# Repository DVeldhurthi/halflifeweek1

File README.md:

# Half-Life Week 1: Design a PCB

Earlier two-layer BeginnerFC layout. The current CAD files in this repository are the four-layer Week1 design.

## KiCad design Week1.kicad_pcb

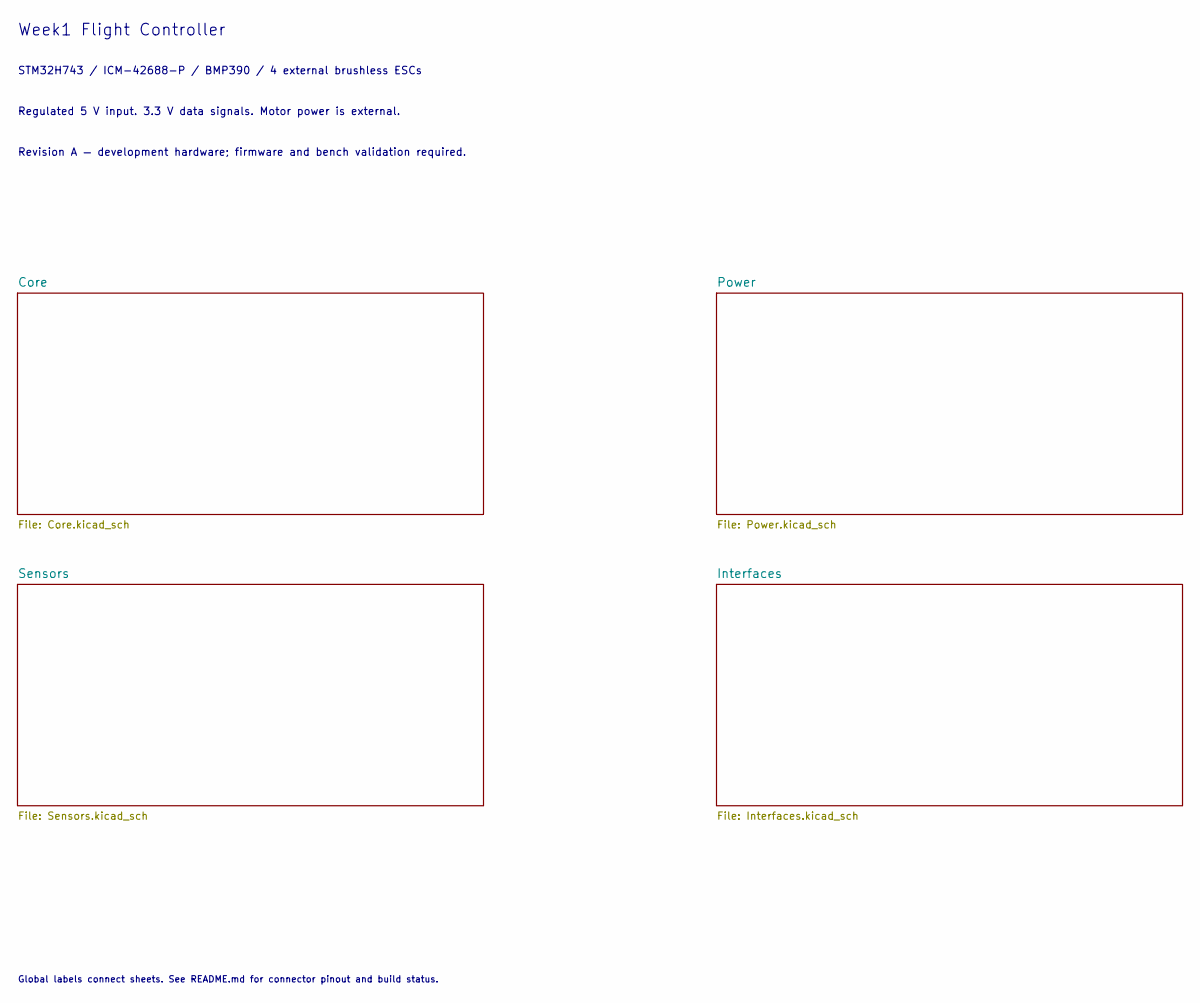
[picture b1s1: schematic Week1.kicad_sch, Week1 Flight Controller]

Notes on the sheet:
Week1 Flight Controller
STM32H743 / ICM-42688-P / BMP390 / 4 external brushless ESCs
Regulated 5 V input. 3.3 V data signals. Motor power is external.
Revision A — development hardware; firmware and bench validation required.
Global labels connect sheets. See README.md for connector pinout and build status.

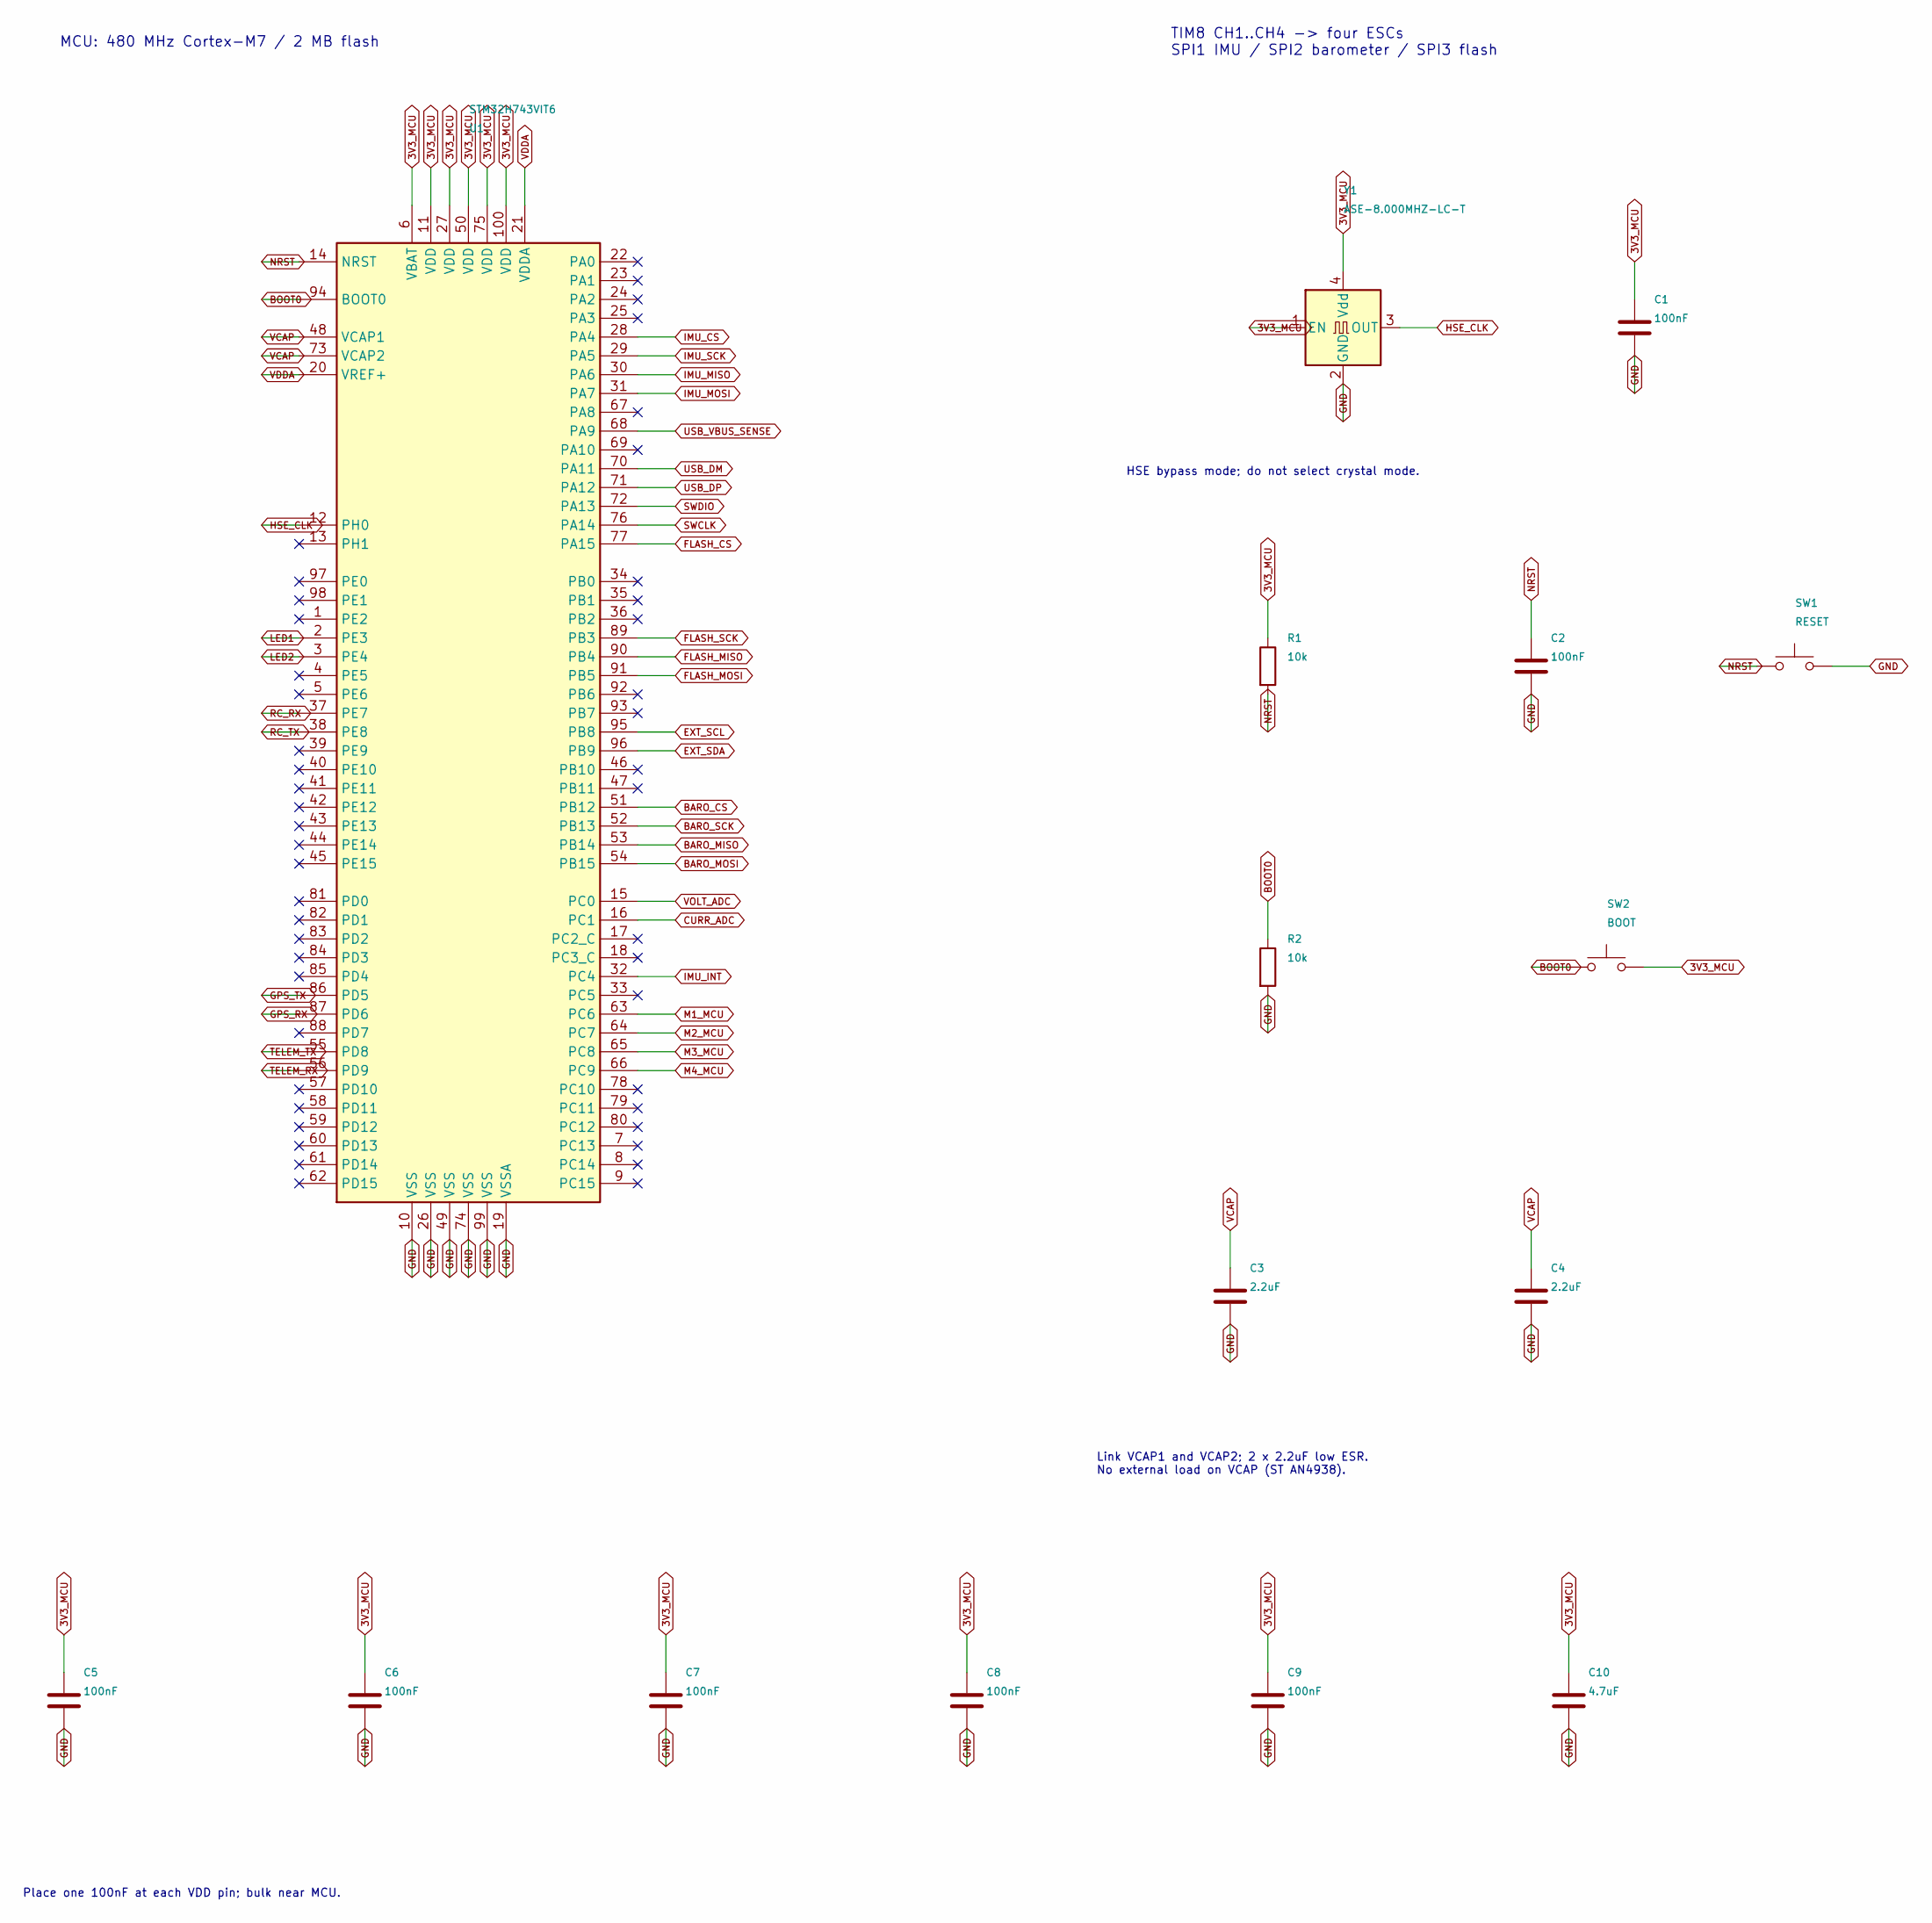
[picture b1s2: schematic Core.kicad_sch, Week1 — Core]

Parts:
C1, C2, C5, C6, C7, C8, C9: 100nF; C_0603_1608Metric
C3, C4: 2.2uF; C_0603_1608Metric
C10: 4.7uF; C_0603_1608Metric
R1, R2: 10k; R_0603_1608Metric
SW1: RESET; SW_SPST_TL3342
SW2: BOOT; SW_SPST_TL3342
U1: STM32H743VIT6; LQFP-100_14x14mm_P0.5mm
Y1: ASE-8.000MHZ-LC-T; Oscillator_SMD_Abracon_ASE-4Pin_3.2x2.5mm

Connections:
3V3_MCU: C1.1, C5.1, C6.1, C7.1, C8.1, C9.1, C10.1, R1.1, SW2.2, U1.6 (VBAT), U1.11 (VDD), U1.27 (VDD), U1.50 (VDD), U1.75 (VDD), U1.100 (VDD), Y1.1 (EN), Y1.4 (Vdd); also elsewhere on the board
BARO_CS: U1.51 (PB12); also elsewhere on the board
BARO_MISO: U1.53 (PB14); also elsewhere on the board
BARO_MOSI: U1.54 (PB15); also elsewhere on the board
BARO_SCK: U1.52 (PB13); also elsewhere on the board
BOOT0: R2.1, SW2.1, U1.94 (BOOT0)
CURR_ADC: U1.16 (PC1); also elsewhere on the board
EXT_SCL: U1.95 (PB8); also elsewhere on the board
EXT_SDA: U1.96 (PB9); also elsewhere on the board
FLASH_CS: U1.77 (PA15); also elsewhere on the board
FLASH_MISO: U1.90 (PB4); also elsewhere on the board
FLASH_MOSI: U1.91 (PB5); also elsewhere on the board
FLASH_SCK: U1.89 (PB3); also elsewhere on the board
GND: C1.2, C2.2, C3.2, C4.2, C5.2, C6.2, C7.2, C8.2, C9.2, C10.2, R2.2, SW1.2, U1.10 (VSS), U1.19 (VSSA), U1.26 (VSS), U1.49 (VSS), U1.74 (VSS), U1.99 (VSS), Y1.2 (GND); also elsewhere on the board
GPS_RX: U1.87 (PD6); also elsewhere on the board
GPS_TX: U1.86 (PD5); also elsewhere on the board
HSE_CLK: U1.12 (PH0), Y1.3 (OUT)
IMU_CS: U1.28 (PA4); also elsewhere on the board
IMU_INT: U1.32 (PC4); also elsewhere on the board
IMU_MISO: U1.30 (PA6); also elsewhere on the board
IMU_MOSI: U1.31 (PA7); also elsewhere on the board
IMU_SCK: U1.29 (PA5); also elsewhere on the board
LED1: U1.2 (PE3); also elsewhere on the board
LED2: U1.3 (PE4); also elsewhere on the board
M1_MCU: U1.63 (PC6); also elsewhere on the board
M2_MCU: U1.64 (PC7); also elsewhere on the board
M3_MCU: U1.65 (PC8); also elsewhere on the board
M4_MCU: U1.66 (PC9); also elsewhere on the board
NRST: C2.1, R1.2, SW1.1, U1.14 (NRST); also elsewhere on the board
RC_RX: U1.37 (PE7); also elsewhere on the board
RC_TX: U1.38 (PE8); also elsewhere on the board
SWCLK: U1.76 (PA14); also elsewhere on the board
SWDIO: U1.72 (PA13); also elsewhere on the board
TELEM_RX: U1.56 (PD9); also elsewhere on the board
TELEM_TX: U1.55 (PD8); also elsewhere on the board
USB_DM: U1.70 (PA11); also elsewhere on the board
USB_DP: U1.71 (PA12); also elsewhere on the board
USB_VBUS_SENSE: U1.68 (PA9); also elsewhere on the board
VCAP: C3.1, C4.1, U1.48 (VCAP1), U1.73 (VCAP2)
VDDA: U1.20 (VREF+), U1.21 (VDDA); also elsewhere on the board
VOLT_ADC: U1.15 (PC0); also elsewhere on the board

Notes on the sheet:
MCU: 480 MHz Cortex-M7 / 2 MB flash
TIM8 CH1..CH4 -> four ESCs SPI1 IMU / SPI2 barometer / SPI3 flash
HSE bypass mode; do not select crystal mode.
Link VCAP1 and VCAP2; 2 x 2.2uF low ESR. No external load on VCAP (ST AN4938).
Place one 100nF at each VDD pin; bulk near MCU.

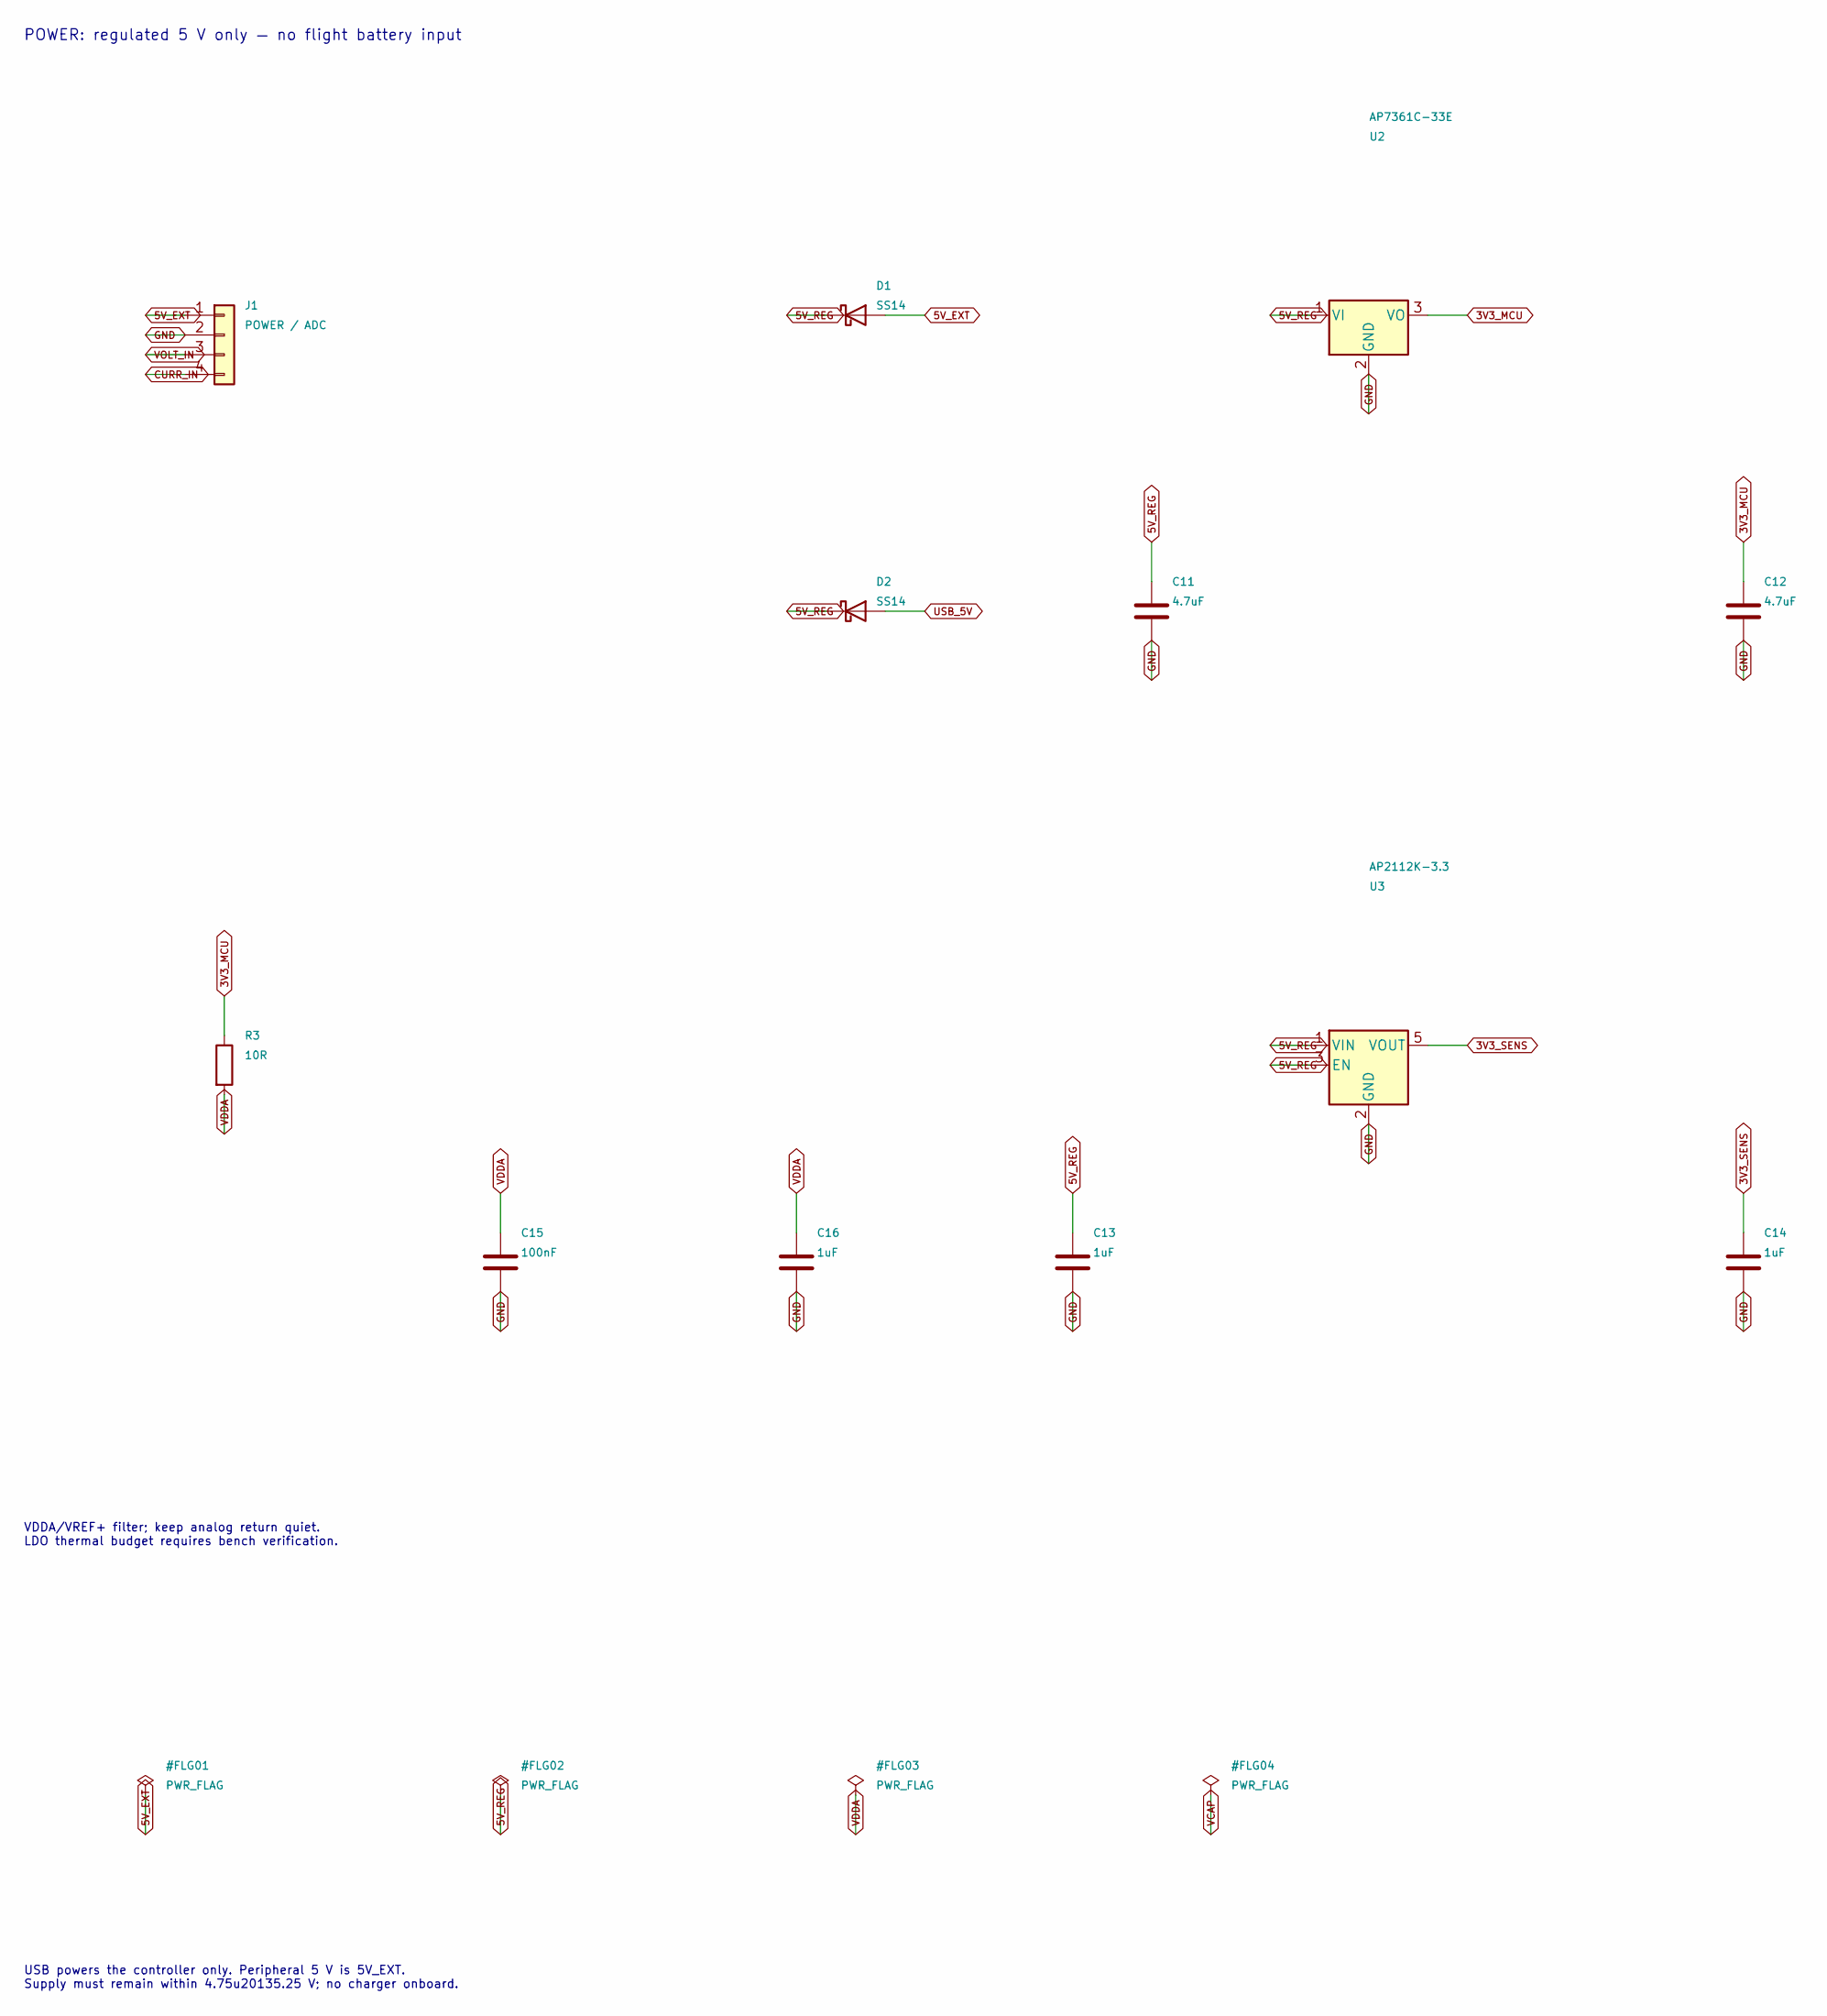
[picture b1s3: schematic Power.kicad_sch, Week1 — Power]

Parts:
C11, C12: 4.7uF; C_0603_1608Metric
C13, C14, C16: 1uF; C_0603_1608Metric
C15: 100nF; C_0603_1608Metric
D1, D2: SS14; D_SMA
J1: POWER / ADC; JST_GH_SM04B-GHS-TB_1x04-1MP_P1.25mm_Horizontal
R3: 10R; R_0603_1608Metric
U2: AP7361C-33E; SOT-223-3_TabPin2
U3: AP2112K-3.3; SOT-23-5

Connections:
3V3_MCU: C12.1, R3.1, U2.3 (VO); also elsewhere on the board
3V3_SENS: C14.1, U3.5 (VOUT); also elsewhere on the board
5V_EXT: D1.2 (A), J1.1; also elsewhere on the board
5V_REG: C11.1, C13.1, D1.1 (K), D2.1 (K), U2.1 (VI), U3.1 (VIN), U3.3 (EN)
CURR_IN: J1.4; also elsewhere on the board
GND: C11.2, C12.2, C13.2, C14.2, C15.2, C16.2, J1.2, U2.2 (GND), U3.2 (GND); also elsewhere on the board
USB_5V: D2.2 (A); also elsewhere on the board
VDDA: C15.1, C16.1, R3.2; also elsewhere on the board
VOLT_IN: J1.3; also elsewhere on the board

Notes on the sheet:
POWER: regulated 5 V only — no flight battery input
VDDA/VREF+ filter; keep analog return quiet. LDO thermal budget requires bench verification.
USB powers the controller only. Peripheral 5 V is 5V_EXT. Supply must remain within 4.75u20135.25 V; no charger onboard.

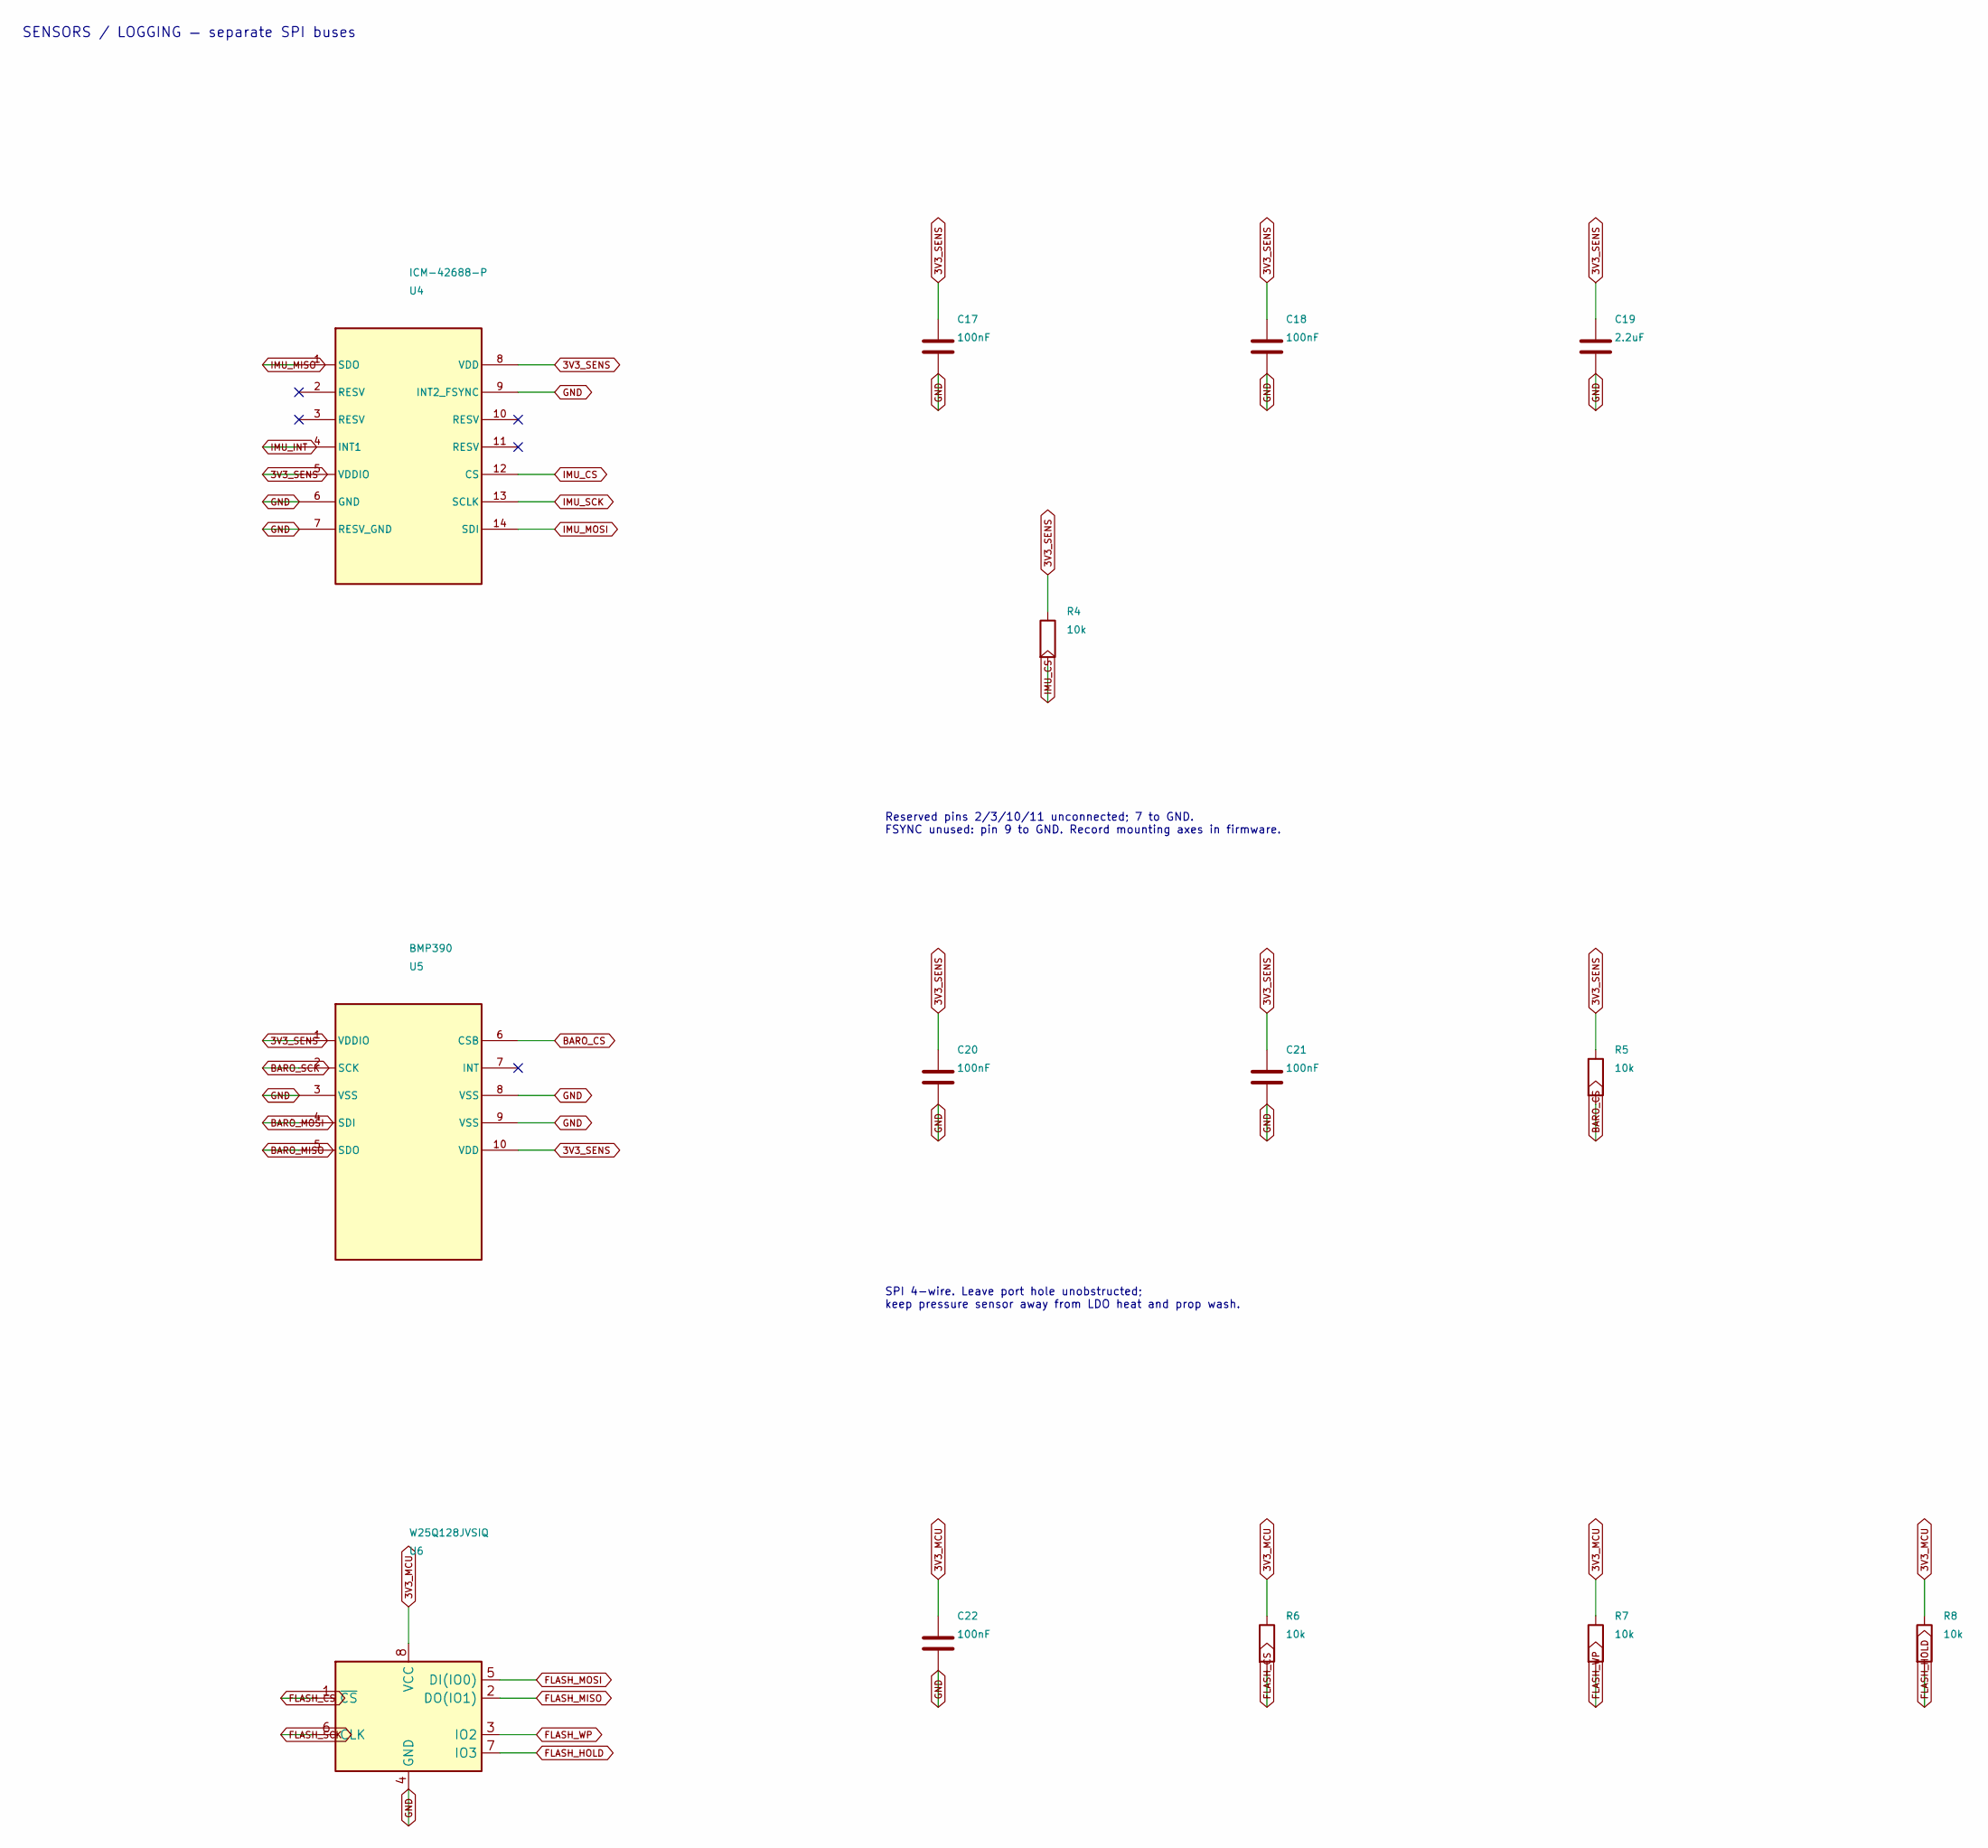
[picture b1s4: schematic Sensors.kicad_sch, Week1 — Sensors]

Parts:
C17, C18, C20, C21, C22: 100nF; C_0603_1608Metric
C19: 2.2uF; C_0603_1608Metric
R4, R5, R6, R7, R8: 10k; R_0603_1608Metric
U4: ICM-42688-P
U5: BMP390
U6: W25Q128JVSIQ; SOIC-8_5.23x5.23mm_P1.27mm

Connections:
3V3_MCU: C22.1, R6.1, R7.1, R8.1, U6.8 (VCC); also elsewhere on the board
3V3_SENS: C17.1, C18.1, C19.1, C20.1, C21.1, R4.1, R5.1, U4.5 (VDDIO), U4.8 (VDD), U5.1 (VDDIO), U5.10 (VDD); also elsewhere on the board
BARO_CS: R5.2, U5.6 (CSB); also elsewhere on the board
BARO_MISO: U5.5 (SDO); also elsewhere on the board
BARO_MOSI: U5.4 (SDI); also elsewhere on the board
BARO_SCK: U5.2 (SCK); also elsewhere on the board
FLASH_CS: R6.2, U6.1 (~CS); also elsewhere on the board
FLASH_HOLD: R8.2, U6.7 (IO3)
FLASH_MISO: U6.2 (DO(IO1)); also elsewhere on the board
FLASH_MOSI: U6.5 (DI(IO0)); also elsewhere on the board
FLASH_SCK: U6.6 (CLK); also elsewhere on the board
FLASH_WP: R7.2, U6.3 (IO2)
GND: C17.2, C18.2, C19.2, C20.2, C21.2, C22.2, U4.6 (GND), U4.7 (RESV_GND), U4.9 (INT2_FSYNC), U5.3 (VSS), U5.8 (VSS), U5.9 (VSS), U6.4 (GND); also elsewhere on the board
IMU_CS: R4.2, U4.12 (CS); also elsewhere on the board
IMU_INT: U4.4 (INT1); also elsewhere on the board
IMU_MISO: U4.1 (SDO); also elsewhere on the board
IMU_MOSI: U4.14 (SDI); also elsewhere on the board
IMU_SCK: U4.13 (SCLK); also elsewhere on the board

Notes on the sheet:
SENSORS / LOGGING — separate SPI buses
Reserved pins 2/3/10/11 unconnected; 7 to GND. FSYNC unused: pin 9 to GND. Record mounting axes in firmware.
SPI 4-wire. Leave port hole unobstructed; keep pressure sensor away from LDO heat and prop wash.
